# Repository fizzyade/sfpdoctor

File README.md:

[uri_license]: https://www.gnu.org/licenses/gpl-3.0.en.html
[uri_license_image]: https://img.shields.io/badge/License-GPLv3-blue.svg

[![License: GPLv3][uri_license_image]][uri_license]

# SFP Doctor
SFP Doctor is an open source hardware &amp; software project for reading and writing the EEPROM inside SFP &amp; SFP+ modules.

## About

SFP modules contain an EEPROM which contains information about the module.  This information includes the OUI (Organizationally Unique Identifier) which identifies the vendor of the module.

Some NIC's and switches are locked to using a particular vendors own SFP modules, this hardware and software project provides a tool for reading and modifying this information (providing the vendor has not disabled write access to the EEPROM).

The hardware design is intended to be as simple and cheap as possible, therefore it makes use of the [Cypress CYC8CKIT-059](https://www.cypress.com/documentation/development-kitsboards/cy8ckit-059-psoc-5lp-prototyping-kit-onboard-programmer-and) prototyping board as the USB interface to the EEPROM on the module, this board is readily and cheaply available.

## Repository Contents

* **/hardware** - [KiCad](https://kicad.org/) schematic and PCB layout source files.
* **/firmware** - The firmware for the [CY8C5888LTI-LP097](https://www.cypress.com/part/cy8c5888lti-lp097) microcontroller on the [Cypress CYC8CKIT-059](https://www.cypress.com/documentation/development-kitsboards/cy8ckit-059-psoc-5lp-prototyping-kit-onboard-programmer-and) prototyping board.
* **/software** - The desktop software to control the hardware.
* **/drivers** - Platform dependent drivers for the hardware interface.

Development takes place in the develop branch, master is currently a placeholder and not up to date.

## Required Tools

* **[Cypress PSoC Creator](https://www.cypress.com/products/psoc-creator-integrated-design-environment-ide)** for firmware development.
* **[KiCad](https://kicad.org/)** for hardware design.
* **[Node.js](https://nodejs.org/)** for desktop software.
* **[Yarn](https://yarnpkg.com/)** for desktop software.
* **[ELECTRON](https://electronjs.org/)** for desktop software development.

## Building Software

### Desktop

After installing the prequestite packages, use the following commands.

    yarn run build
    yarn run start

The platform binary can be created with the following commands.

    yarn run build
    yarn run dist

(*Please note that currently the software is not functional*)

### Firmware

Open the firmware project in PSOC Creator and select build to create the firmware image.

## Project Status

### Hardware

* **Design:** Complete.
* **Manufacture:** Complete.
    * _**07 Nov 2019**_ - Board Assembled, ready for test.
    * _**10 Nov 2019**_ - Board tested and working.

(_please **NOTE:** in this picture the CY8CKIT-059 module is installed the wrong way around, picture to be updated soon.)_

(_Render of Rev. 1.3 board_)

### Firmware

* **Development:** Started.

### Software

* **Development:** Started.

## With Thanks

This project is using a USB VID & PID kindly allocated by [pid.codes](http://pid.codes).  Their repository can be found [here](https://github.com/pidcodes/pidcodes.github.com).  They support open source development by providing VID/PID pairs for free.

## License

This project is open source and the entire project is released under the [GPLv3 license](https://www.gnu.org/licenses/gpl-3.0.en.html).

Distributed as-is; no warranty is given.

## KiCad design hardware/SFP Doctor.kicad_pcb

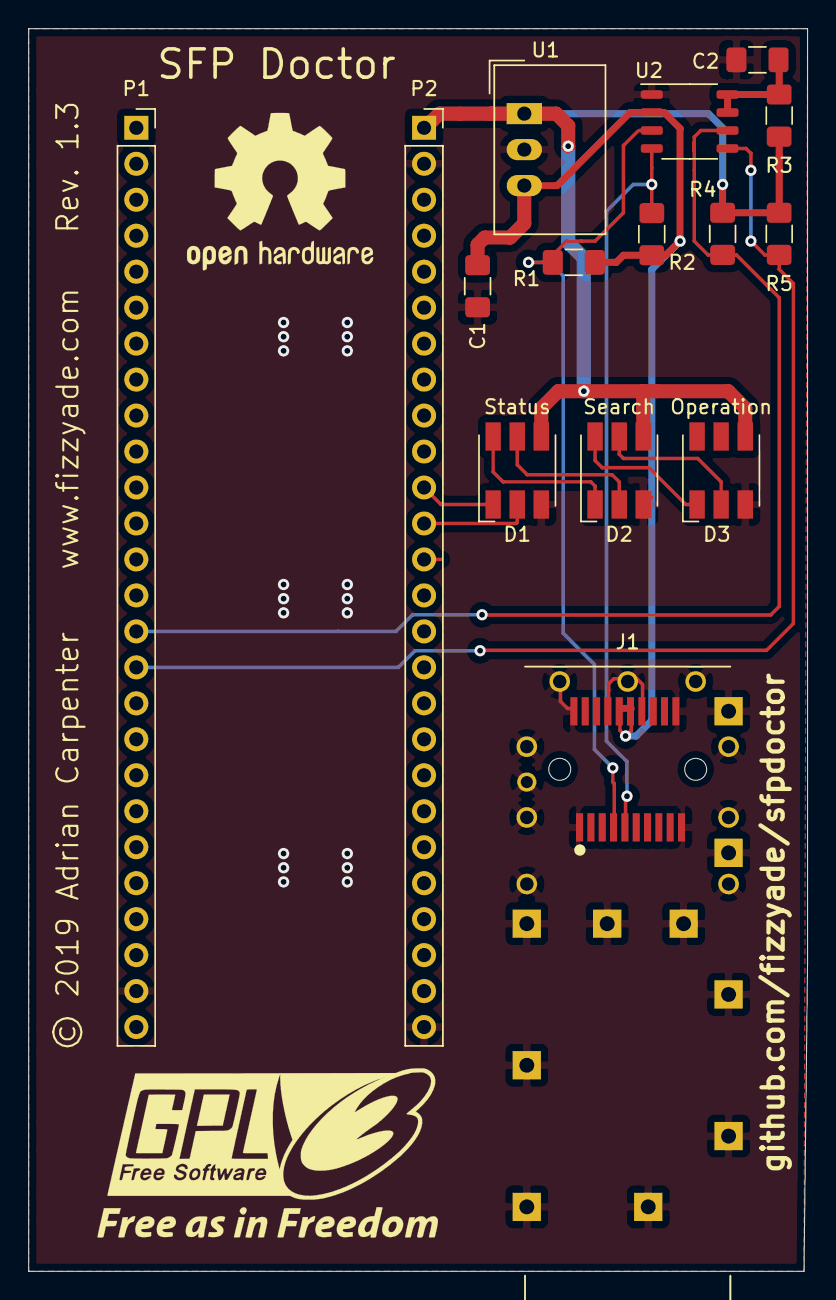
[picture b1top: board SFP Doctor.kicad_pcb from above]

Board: 2 copper layers, 55.0 x 87.8 mm, 15 parts (0 on the bottom side), 14 nets.

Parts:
C1, C2: 100nF; C_1206_3216Metric_Pad1.42x1.75mm_HandSolder
D1, D2, D3: APA102; LED_RGB_5050-6
J1: 2227023-1; TE_2227023-1
P1, P2: CONN_01X26; PinSocket_1x26_P2.54mm_Vertical
R1, R2, R4, R5: 4K7; R_1206_3216Metric_Pad1.42x1.75mm_HandSolder
R3: 200K; R_1206_3216Metric_Pad1.42x1.75mm_HandSolder
U1: TSR_1-2433; Converter_DCDC_TRACO_TSR-1_THT
U2: PCA9306; SSOP-8_3.9x5.05mm_P1.27mm

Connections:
+3V3: C1.1, J1.15, J1.16, R1.1, R2.1, U1.3, U2.2
+5V: D1.4, D2.4, D3.4, P2.1, R3.1, R4.1, R5.1, U1.1
GND: C1.2, C2.2, D1.3, D2.3, D3.3, J1.1, J1.10, J1.11, J1.14, J1.17, J1.20, J1.S1, J1.S2, J1.S3, J1.S4, J1.S5, J1.S6, J1.S7, J1.S8, J1.S9, J1.S10, J1.S11, J1.S12, J1.S13, J1.S14, J1.S15, J1.S16, J1.S17, J1.S18, J1.S19, J1.S20, P1.25, P2.2, P2.26, U1.2, U2.1
LED_CLOCK: D1.2, P2.12
LED_DATA: D1.1, P2.11
unnamed: C2.1, R3.2, U2.7, U2.8
unnamed: D1.5, D2.2
unnamed: D1.6, D2.1
unnamed: D2.5, D3.2
unnamed: D2.6, D3.1
SCL_3V3: J1.5, R2.2, U2.4
SCL_5V: P1.16, R5.2, U2.5
SDA_3V3: J1.4, R1.2, U2.3
SDA_5V: P1.15, R4.2, U2.6

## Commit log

2019-09-26 repo: initial commit
2019-09-26 repo: updated README.md
2019-09-27 chore(package): Added Windows device driver binaries
2019-09-27 repo(firmware): Added initial firmware project
2019-09-30 wip: initial development
2019-09-30 wip: added GPL header to source files
2019-10-04 wip: changes for USB
    - VID/PID allocated by pid.codes
    - Driver .inf modified for new VID/PID
    - Firmware modified for new VID/PID
    - Added Windows PowerShell script to create code signing certificate
    - Added Windows PowerShell script for generating driver .cat file and signing the driver
    - README.md modified to include links to pid.codes
2019-10-04 wip: refactoring application architecture
2019-10-05 chore: applied development stash
2019-10-06 chore: switched project to using yarn
2019-10-06 chore: modified gitignore to allow .vscode in repo
2019-10-07 chore: modified package and tsconfig files
    * Files modified so that electron-builder produces valid application binary images.
    * Added and modified the scripts so that the application can be run/debugged/packaged correctly.
2019-10-26 repo(github): added CNAME
2019-11-08 chore: updated schematic
    Missing capacitor values added
    Logos added to schematic
2019-11-08 repo: added icon to README.md
2019-11-08 repo(assets): initial commit
2019-11-08 repo: cleanup
2019-11-08 repo(assets): added photos
2019-11-08 repo: updated README.md
    Added photographs of assembled boards.
2019-11-08 repo: updated README.md
    Fixed broken image links
2019-11-09 repo(assets): updated photographs
    Better resizing algorithm used
2019-11-10 chore(hardware): added pin labels
    added pin labels to the CYC8CKIT-059 symbol
2019-11-11 wip: revision 1.2 of PCB
2019-11-11 repo: added rev 1.2 render
2019-11-11 repo: resized 1.2 board render
2019-11-11 repo: amended image
2019-11-11 wip: revision 1.3 of PCB
    Moved SFP cage
2019-11-12 repo: updated board render
2020-07-07 chore(deps-dev): bump electron in /software/sfpdoctor-app
    Bumps [electron](https://github.com/electron/electron) from 6.1.12 to 9.1.0.
    - [Release notes](https://github.com/electron/electron/releases)
    - [Changelog](https://github.com/electron/electron/blob/master/docs/breaking-changes.md)
    - [Commits](https://github.com/electron/electron/compare/v6.1.12...v9.1.0)
2021-11-08 Update README.md
    https://forum.kicad.info/t/warning-avoid-all-links-to-kicad-pcb-org-use-kicad-org/31521

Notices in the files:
hardware/SFP Doctor.kicad_pcb:
© 2019 Adrian Carpenter
